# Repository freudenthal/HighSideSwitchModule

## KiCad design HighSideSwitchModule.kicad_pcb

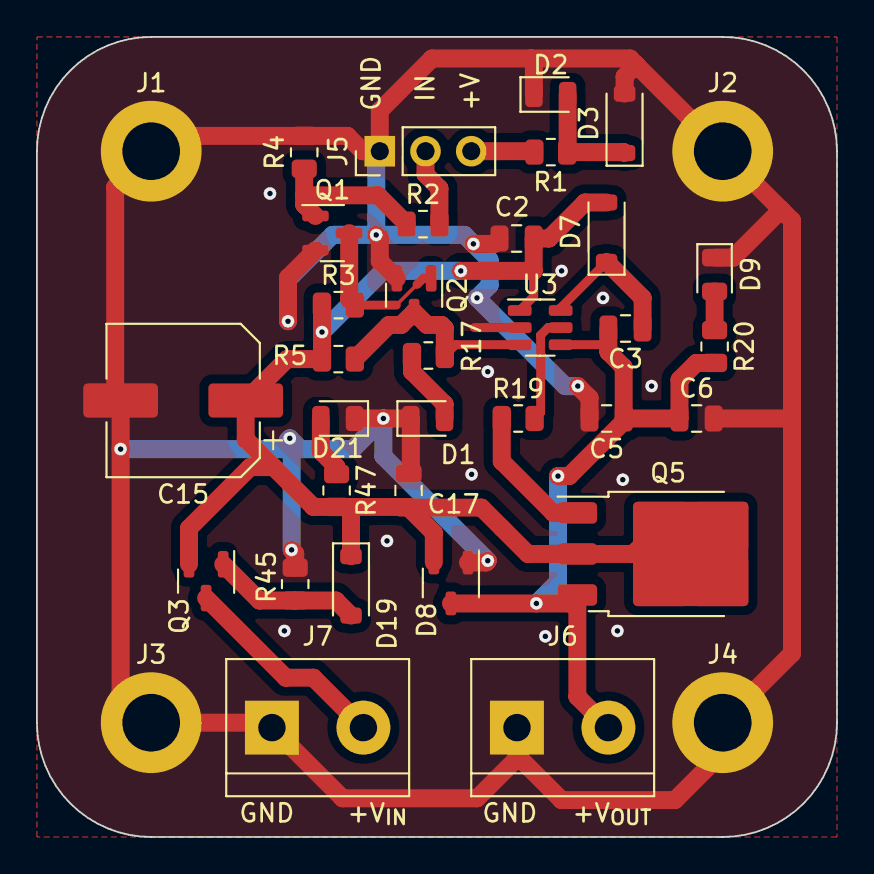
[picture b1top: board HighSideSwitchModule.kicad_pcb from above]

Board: 2 copper layers, 44.5 x 44.5 mm, 36 parts (0 on the bottom side), 17 nets.

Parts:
C2, C3, C6, C17: 1uF; C_0805_2012Metric
C5: 10uF; C_0805_2012Metric
C15: 100uF; CP_Elec_8x11.9
D1, D2, D9, D21: LED; LED_0805_2012Metric
D3, D19: 10V; D_SOD-123
D7: D; D_SOD-123
D8: 100V; SOT-23-3
J1, J2, J3, J4: M3; MountingHole_3.2mm_M3_DIN965_Pad
J5: Input; PinHeader_1x03_P2.54mm_Vertical
J6: VOUT; TerminalBlock_bornier-2_P5.08mm
J7: VIn; TerminalBlock_bornier-2_P5.08mm
Q1, Q2: Q_NMOS_GSD; SOT-23
Q3: Q_PMOS_GSD; SOT-23
Q5: Q_NMOS_GDS; TO-252-3_TabPin2
R1, R20, R47: 1.2kΩ; R_0805_2012Metric
R2, R17: 1kΩ; R_0805_2012Metric
R3, R5: 10kΩ; R_0805_2012Metric
R4, R45: 100kΩ; R_0805_2012Metric
R19: 20Ω; R_0805_2012Metric
U3: IRS2075; SOT-23-6

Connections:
+12V: C2.1, C15.1, C17.1, D7.2 (A), D8.2 (K), D19.1 (K), Q3.2 (S), Q5.2 (D), R3.1, R5.1, R47.2, U3.1 (V_{CC})
/HighSideGate/IN: J5.2, R2.2
GND: C2.2, C5.2, C6.2, C15.2, C17.2, D1.1 (K), D2.1 (K), D3.2 (A), D8.1 (K), D9.1 (K), D21.1 (K), J1.1, J2.1, J3.1, J4.1, J5.1, J6.1, J7.1, Q1.2 (S), Q2.2 (S), R4.2, R45.1, U3.2 (COM)
unnamed: D1.2 (A), R17.1
unnamed: D2.2 (A), D3.1 (K), R1.1
unnamed: C3.1, D7.1 (K), U3.6 (VB)
unnamed: C3.2, C5.1, C6.1, D8.3 (A), J6.2, Q5.3 (S), R20.2, U3.4 (VS)
unnamed: D9.2 (A), R20.1
unnamed: D19.2 (A), Q3.1 (G), R45.2
unnamed: D21.2 (A), R47.1
unnamed: J5.3, R1.2
unnamed: J7.2, Q3.3 (D)
unnamed: Q1.3 (D), Q2.1 (G), R3.2
unnamed: Q1.1 (G), R2.1, R4.1
unnamed: Q2.3 (D), R5.2, R17.2, U3.3 (IN)
unnamed: Q5.1 (G), R19.1
unnamed: R19.2, U3.5 (HO)

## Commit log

2023-12-21 Fixed FETs on input.
